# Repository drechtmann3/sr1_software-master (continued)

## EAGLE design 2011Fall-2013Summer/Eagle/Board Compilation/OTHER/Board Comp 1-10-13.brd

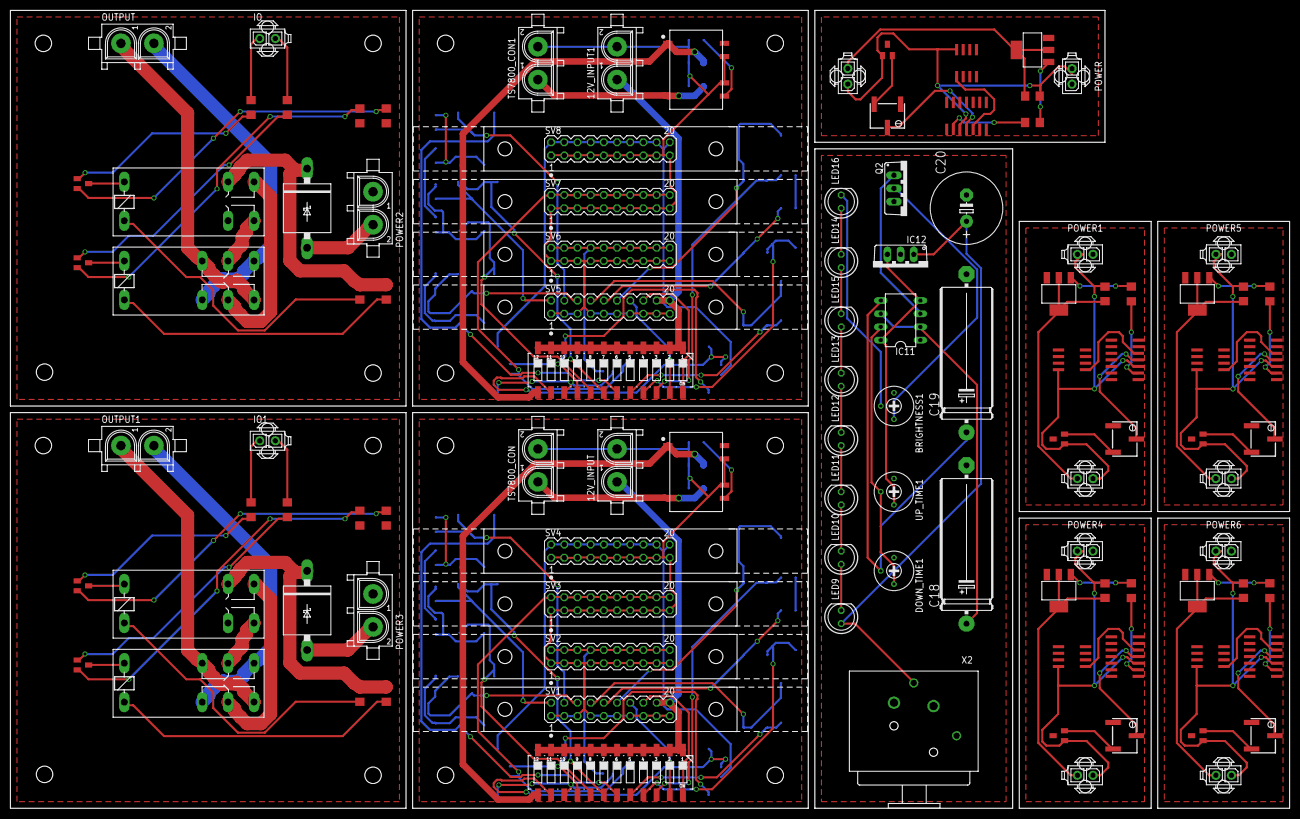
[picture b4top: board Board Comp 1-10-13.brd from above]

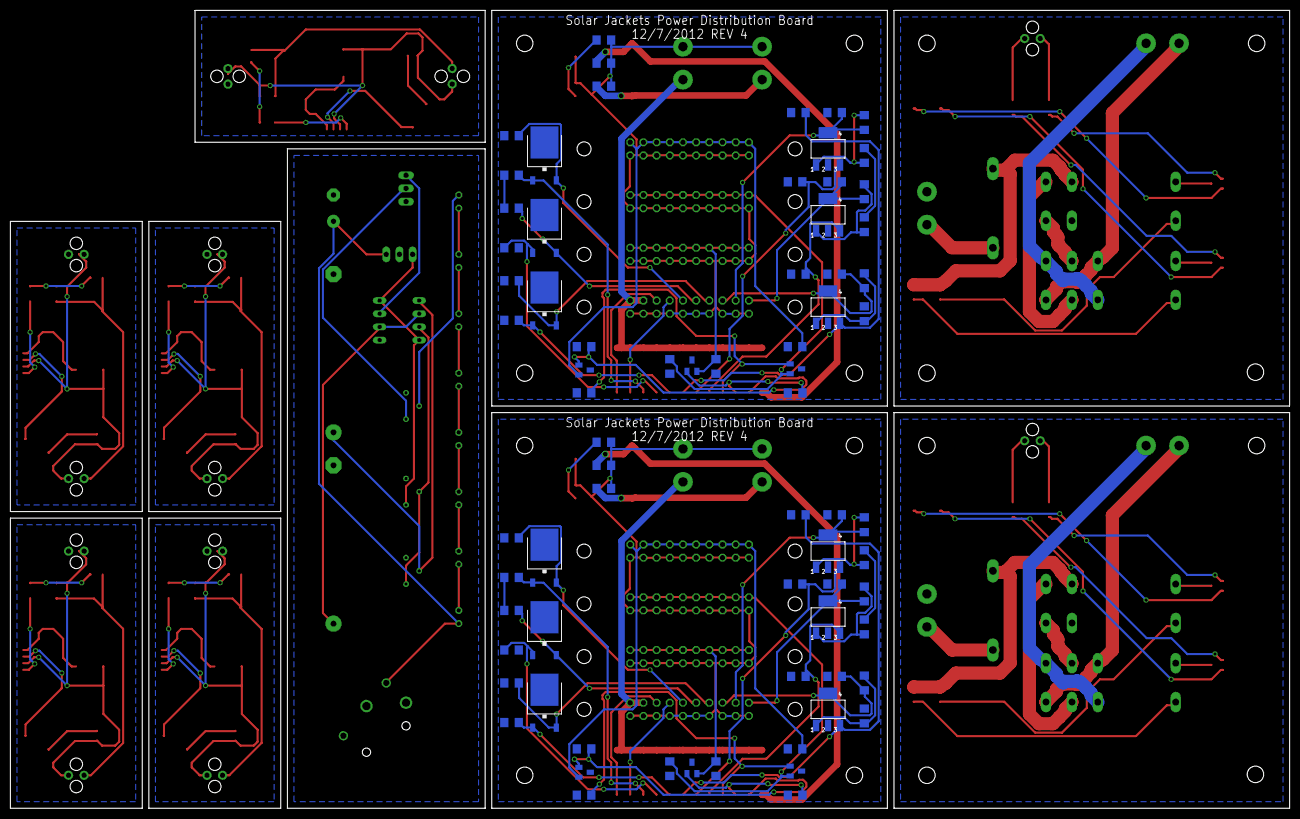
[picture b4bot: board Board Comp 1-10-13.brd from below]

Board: 2 copper layers, 246.4 x 153.7 mm, 179 parts (72 on the bottom side), 146 nets.

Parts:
3V1, 3V2, 3V3, 3V4, 3V5, 3V6: MAX6103; SOT23
12V_INPUT, 12V_INPUT1: 350759-4
317CAP1, 317CAP3, 317CAP4, 317CAP6, 317CAP9, 317CAP11: .33uF; C1206
317CAP2, 317CAP5, 317CAP7, 317CAP8, 317CAP10, 317CAP12, 6103CAP1, 6103CAP2, 6103CAP3, 6103CAP4, 6103CAP5, 6103CAP6, 6103CAP7, 6103CAP8, 6103CAP9, 6103CAP10, 6103CAP11, 6103CAP12: 1uF; C1206
BRIGHTNESS1: 10 k; RTRIM3339P
C1, C2, C15, C16, C21: 1 uF; C1206
C3, C4, C5, C6, C7, C8, C9, C10, C11, C12, C13, C14: 1uF; C1206
C18, C19: 1uF; E30-10
C20: 1000uF; E5-13
D1, D3: 6A4; P6T15
DOWN_TIME1: 10k; RTRIM3339P
IC1, IC2, IC9, IC10, IC13: LM339D; SO14
IC3, IC4, IC5, IC6, IC7, IC8: LM317; SOT223
IC11: ICM7555; DIL08
IC12: 7805TV; TO220V
IO, IO1: 794681-2
J1, J2, J3, J4, J5: 794681-2
K1, K3: G2R2
K2, K4: G2R2A
LED9, LED10, LED11, LED12, LED13, LED14, LED15, LED16: LED5MM
OUTPUT, OUTPUT1: 350428-1
POWER, POWER1, POWER4, POWER5, POWER6: 794681-2
POWER2, POWER3: 350428-1
PWR_1, PWR_2, PWR_3, PWR_4, PWR_5, PWR_6: 7805DT; TO252
Q2: IRF512; TO220BV
R1, R2, R27, R28, R29: 10k; RTRIMTS63Y
R3, R5, R7, R9, R11, R13: 220; R1206
R4, R6, R8, R10, R12, R14: 361; R1206
R15, R16, R17, R18, R21, R22, R23, R24: 1k; R1206
R19, R20, R25, R26: 0; R1206
S1, S2: 219-12; CTS-219-12
SV1, SV2, SV3, SV4, SV5, SV6, SV7, SV8: AMPLATCH-20; MA10-2
T1, T2, T3, T4: PMV56XN; SOT23
TS7800_CON, TS7800_CON1: 350759-4
U$1, U$5, U$11, U$15, U$19: 100; R1206
U$2, U$6, U$12, U$16, U$20: MAX6103; SOT23
U$3, U$7, U$13, U$17, U$21: NDT3055; SOT223
U$4, U$8, U$14, U$18, U$22: LM35; SO-08
U$9, U$10: V7805
UP_TIME1: 10k; RTRIM3339P
V7805_C1, V7805_C2, V7805_C3, V7805_C4, V7805_C5, V7805_C6: 1uF; C1206
X2: NC3FAH2

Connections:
3.3V1: 317CAP8.1, IC4.4, R7.1, SV1.6
3.3V1_EN: 317CAP3.1, IC4.3, S1.19
3.3V1_EN1: 317CAP1.1, IC3.3, S2.19
3.3V2: 317CAP10.1, IC5.4, R9.1, SV1.4
3.3V2_EN: 317CAP9.1, IC5.3, S1.18
3.3V2_EN1: 317CAP4.1, IC7.3, S2.18
3.3V3: 317CAP12.1, IC6.4, R11.1, SV1.2
3.3V3_EN: 317CAP11.1, IC6.3, S1.17
3.3V3_EN1: 317CAP6.1, IC8.3, S2.17
3.3V4: 317CAP7.1, IC8.4, R13.1, SV5.2
3.3V5: 317CAP2.1, IC3.4, R3.1, SV5.6
3.3V6: 317CAP5.1, IC7.4, R5.1, SV5.4
5V1: C4.1, PWR_1.2, SV1.12
5V1_EN: C3.1, PWR_1.1, S1.22
5V1_EN1: C9.1, PWR_4.1, S2.22
5V2: C6.1, PWR_2.2, SV1.10
5V2_EN: C5.1, PWR_2.1, S1.21
5V2_EN1: C11.1, PWR_5.1, S2.21
5V3: C7.1, PWR_3.2, SV1.8
5V3_EN: C8.1, PWR_3.1, S1.20
5V3_EN1: C14.1, PWR_6.1, S2.20
5V4: C13.1, PWR_6.2, SV5.8
5V5: C12.1, PWR_5.2, SV5.10
5V6: C10.1, PWR_4.2, SV5.12
5V7: IC11.4, IC11.8, IC12.3, UP_TIME1.3
12V: C1.1, IC1.3, J2.1, POWER.2, U$2.1, U$4.8
12V1: C2.1, IC2.3, J1.1, POWER1.2, U$6.1, U$8.8
12V1_EN: S1.24, SV1.16
12V1_EN1: S2.24, SV5.16
12V2: 12V_INPUT.1, S1.1, S1.2, S1.3, S1.4, S1.5, S1.6, S1.7, S1.8, S1.9, S1.10, S1.11, S1.12, SV1.18, SV1.20
12V2_EN: S1.23, SV1.14
12V2_EN1: S2.23, SV5.14
12V3: 12V_INPUT1.1, S2.1, S2.2, S2.3, S2.4, S2.5, S2.6, S2.7, S2.8, S2.9, S2.10, S2.11, S2.12, SV5.18, SV5.20
12V4: D3.C, K2.P1, R15.2, R16.2
12V5: D1.C, K4.P1, R21.2, R22.2
12V6: C21.1, IC13.3, J3.1, POWER4.2, U$12.1, U$14.8
12V7: C15.1, IC9.3, J4.1, POWER5.2, U$16.1, U$18.8
12V8: C16.1, IC10.3, J5.1, POWER6.2, U$20.1, U$22.8
12V_PRE: D3.A, POWER2.2
12V_PRE1: D1.A, POWER3.2
24V1: C20.+, IC12.1, LED9.A, X2.3
DIR: IO.2, R17.2
DIR1: IO1.2, R23.2
GND: IC1.12, POWER.1, R1.1, U$2.3, U$3.3, U$4.4
GND1: IC2.12, POWER1.1, R2.1, U$6.3, U$7.3, U$8.4
GND2: 3V3.3, 3V4.3, 3V5.3, 12V_INPUT.2, 317CAP3.2, 317CAP8.2, 317CAP9.2, 317CAP10.2, 317CAP11.2, 317CAP12.2, 6103CAP7.2, 6103CAP8.2, 6103CAP9.2, 6103CAP10.2, 6103CAP11.2, 6103CAP12.2, C3.2, C4.2, C5.2, C6.2, C7.2, C8.2, PWR_1.3, PWR_2.3, PWR_3.3, R8.2, R10.2, R12.2, SV1.1, SV1.3, SV1.5, SV1.7, SV1.9, SV1.11, SV1.13, SV1.15, SV1.17, SV1.19, SV2.1, SV2.3, SV2.5, SV2.7, SV2.9, SV2.11, SV2.13, SV2.15, SV2.17, SV2.19, SV3.1, SV3.3, SV3.5, SV3.7, SV3.9, SV3.11, SV3.13, SV3.15, SV3.17, SV3.19, SV4.1, SV4.3, SV4.5, SV4.7, SV4.9, SV4.11, SV4.13, SV4.15, SV4.17, SV4.19, TS7800_CON.2, U$9.7, U$9.9, V7805_C4.2, V7805_C5.2, V7805_C6.2
GND3: 3V1.3, 3V2.3, 3V6.3, 12V_INPUT1.2, 317CAP1.2, 317CAP2.2, 317CAP4.2, 317CAP5.2, 317CAP6.2, 317CAP7.2, 6103CAP1.2, 6103CAP2.2, 6103CAP3.2, 6103CAP4.2, 6103CAP5.2, 6103CAP6.2, C9.2, C10.2, C11.2, C12.2, C13.2, C14.2, PWR_4.3, PWR_5.3, PWR_6.3, R4.2, R6.2, R14.2, SV5.1, SV5.3, SV5.5, SV5.7, SV5.9, SV5.11, SV5.13, SV5.15, SV5.17, SV5.19, SV6.1, SV6.3, SV6.5, SV6.7, SV6.9, SV6.11, SV6.13, SV6.15, SV6.17, SV6.19, SV7.1, SV7.3, SV7.5, SV7.7, SV7.9, SV7.11, SV7.13, SV7.15, SV7.17, SV7.19, SV8.1, SV8.3, SV8.5, SV8.7, SV8.9, SV8.11, SV8.13, SV8.15, SV8.17, SV8.19, TS7800_CON1.2, U$10.7, U$10.9, V7805_C1.2, V7805_C2.2, V7805_C3.2
GND4: IC9.12, POWER5.1, R28.1, U$16.3, U$17.3, U$18.4
GND5: C18.-, C19.-, C20.-, IC11.1, IC12.2, Q2.S, X2.1
GND6: K2.P2, POWER2.1, R19.1, R20.1
GND7: K4.P2, POWER3.1, R25.1, R26.1
GND8: IC13.12, POWER4.1, R27.1, U$12.3, U$13.3, U$14.4
GND9: IC10.12, POWER6.1, R29.1, U$20.3, U$21.3, U$22.4
MOTOR+: K1.O2, K1.S1, OUTPUT.2
MOTOR+1: K3.O2, K3.S1, OUTPUT1.2
MOTOR-: K1.O1, K1.S2, OUTPUT.1
MOTOR-1: K3.O1, K3.S2, OUTPUT1.1
unnamed: IC1.2, U$1.1
unnamed: U$1.2, U$3.1
unnamed: IC1.4, R1.2
unnamed: R1.3, U$2.2
unnamed: C1.2, J2.2, U$3.2, U$3.4
unnamed: IC2.2, U$5.1
unnamed: IC2.4, R2.2
unnamed: IC1.5, U$4.1
unnamed: R2.3, U$6.2
unnamed: U$5.2, U$7.1
unnamed: C2.2, J1.2, U$7.2, U$7.4
unnamed: IC2.5, U$8.1
unnamed: IC4.1, R7.2, R8.1
unnamed: IC5.1, R9.2, R10.1
unnamed: IC6.1, R11.2, R12.1
unnamed: U$9.6, V7805_C4.1
unnamed: IC3.1, R3.2, R4.1
unnamed: IC7.1, R5.2, R6.1
unnamed: IC8.1, R13.2, R14.1
unnamed: U$10.6, V7805_C1.1
unnamed: IC9.2, U$15.1
unnamed: IC9.4, R28.2
unnamed: R28.3, U$16.2
unnamed: U$15.2, U$17.1
unnamed: C15.2, J4.2, U$17.2, U$17.4
unnamed: IC9.5, U$18.1
unnamed: IC10.2, U$19.1
unnamed: IC10.4, R29.2
unnamed: R29.3, U$20.2
unnamed: U$19.2, U$21.1
unnamed: C16.2, J5.2, U$21.2, U$21.4
unnamed: IC10.5, U$22.1
unnamed: C18.+, IC11.2, IC11.6
unnamed: C19.+, DOWN_TIME1.2, IC11.5
unnamed: DOWN_TIME1.3, IC11.7, UP_TIME1.2
unnamed: LED9.K, LED10.A
unnamed: LED10.K, LED11.A
unnamed: LED11.K, LED12.A
unnamed: LED12.K, LED13.A
unnamed: LED13.K, LED15.A
unnamed: LED14.A, LED15.K
unnamed: LED14.K, LED16.A
unnamed: BRIGHTNESS1.2, LED16.K
unnamed: BRIGHTNESS1.3, Q2.D
unnamed: IC11.3, Q2.G
unnamed: K1.P2, K2.S1
unnamed: K1.P1, K2.S2
unnamed: K1.1, R15.1
unnamed: K2.1, R16.1
unnamed: K1.2, T1.3
unnamed: K2.2, T2.3
unnamed: R18.1, T2.1
unnamed: R17.1, T1.1
unnamed: R19.2, T1.2
unnamed: R20.2, T2.2
unnamed: K3.P2, K4.S1
unnamed: K3.P1, K4.S2
unnamed: K3.1, R21.1
unnamed: K4.1, R22.1
unnamed: K3.2, T3.3
unnamed: K4.2, T4.3
unnamed: R24.1, T4.1
unnamed: R23.1, T3.1
unnamed: R25.2, T3.2
unnamed: R26.2, T4.2
unnamed: IC13.2, U$11.1
unnamed: IC13.4, R27.2
unnamed: R27.3, U$12.2
unnamed: U$11.2, U$13.1
unnamed: C21.2, J3.2, U$13.2, U$13.4
unnamed: IC13.5, U$14.1
ON: IO.1, R18.2
ON1: IO1.1, R24.2
TS7800_+: TS7800_CON.1, U$9.5, V7805_C6.1
TS7800_+1: TS7800_CON1.1, U$10.5, V7805_C3.1
TS7800_EN: S1.13, U$9.1, V7805_C5.1
TS7800_EN1: S2.13, U$10.1, V7805_C2.1
VREF1: 3V3.2, 6103CAP8.1, SV3.2, SV3.4, SV3.6, SV3.8, SV3.10, SV3.12, SV3.14, SV3.16, SV3.18, SV3.20
VREF1_EN: 3V3.1, 6103CAP7.1, S1.16
VREF1_EN1: 3V1.1, 6103CAP1.1, S2.16
VREF2: 3V4.2, 6103CAP10.1, SV2.2, SV2.4, SV2.6, SV2.8, SV2.10, SV2.12, SV2.14, SV2.16, SV2.18, SV2.20
VREF2_EN: 3V4.1, 6103CAP9.1, S1.15
VREF2_EN1: 3V2.1, 6103CAP3.1, S2.15
VREF3: 3V5.2, 6103CAP12.1, SV4.2, SV4.4, SV4.6, SV4.8, SV4.10, SV4.12, SV4.14, SV4.16, SV4.18, SV4.20
VREF3_EN: 3V5.1, 6103CAP11.1, S1.14
VREF3_EN1: 3V6.1, 6103CAP5.1, S2.14
VREF4: 3V1.2, 6103CAP2.1, SV7.2, SV7.4, SV7.6, SV7.8, SV7.10, SV7.12, SV7.14, SV7.16, SV7.18, SV7.20
VREF5: 3V2.2, 6103CAP4.1, SV6.2, SV6.4, SV6.6, SV6.8, SV6.10, SV6.12, SV6.14, SV6.16, SV6.18, SV6.20
VREF6: 3V6.2, 6103CAP6.1, SV8.2, SV8.4, SV8.6, SV8.8, SV8.10, SV8.12, SV8.14, SV8.16, SV8.18, SV8.20

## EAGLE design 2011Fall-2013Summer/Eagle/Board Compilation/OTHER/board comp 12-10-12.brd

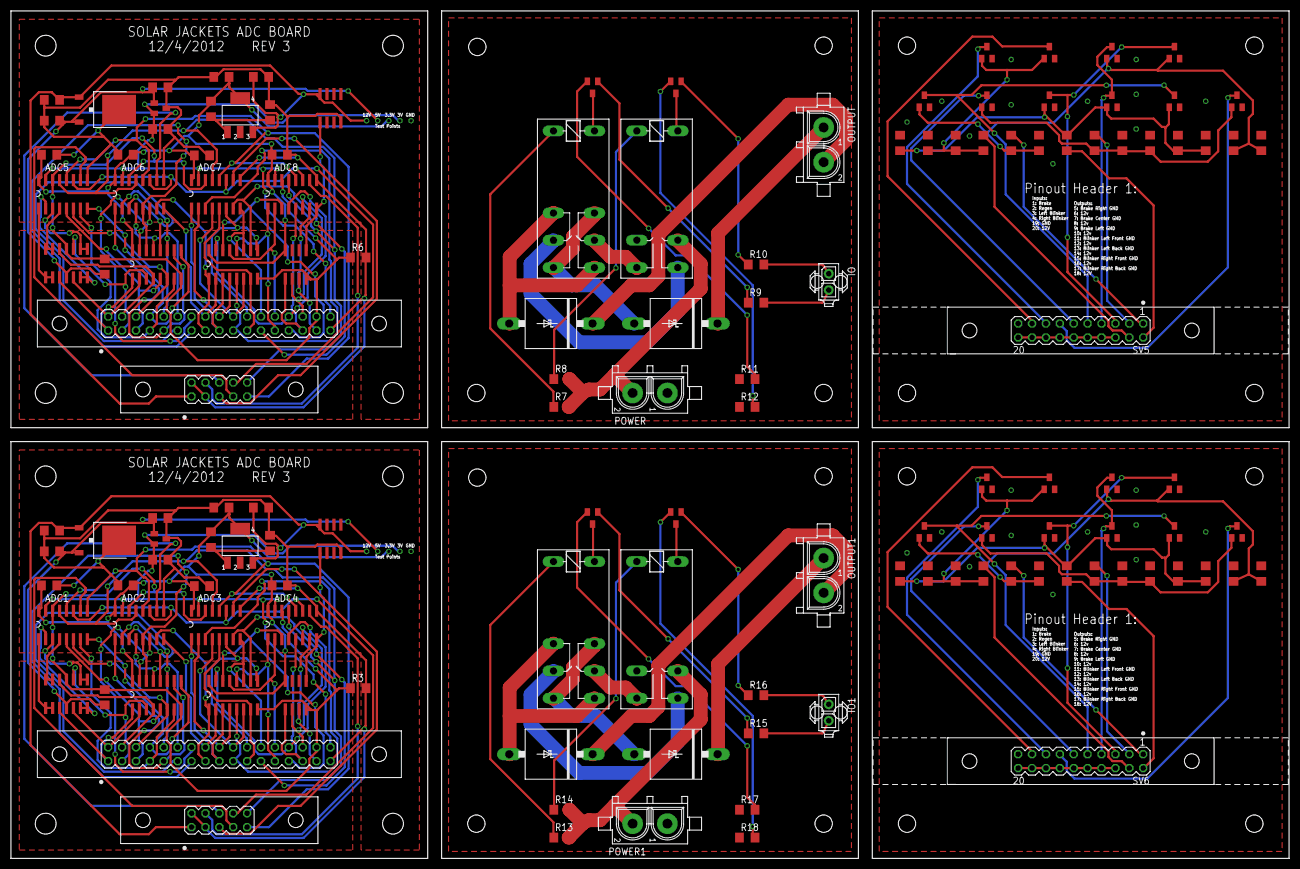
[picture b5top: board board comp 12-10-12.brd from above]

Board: 2 copper layers, 233.7 x 154.9 mm, 136 parts (0 on the bottom side), 170 nets.

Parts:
3V, 3V1: MAX6103; SOT23
5V, 5V1: LM7805TV; TO252
317CAP1, 317CAP3, 7805CAP1, 7805CAP4: .33uF; C1206
317CAP2, 317CAP4, 6103CAP1, 6103CAP2, 6103CAP3, 6103CAP4, 7805CAP2, 7805CAP3: 1uF; C1206
6484CAP1, 6484CAP2: .1uF; C1206
ADC1, ADC2, ADC3, ADC4, ADC5, ADC6, ADC7, ADC8: MCP-3008; SO16
ADC_CAP1, ADC_CAP2, ADC_CAP3, ADC_CAP4, ADC_CAP5, ADC_CAP6, ADC_CAP7, ADC_CAP8: .1uF; C1206
BLINKER-L1, BLINKER-L2, BLINKER-L3, BLINKER-L4: PMV56XN215; SOT23
BLINKER-R1, BLINKER-R2, BLINKER-R3, BLINKER-R4: PMV56XN215; SOT23
BRAKE-C1, BRAKE-C2, BRAKE-C3, BRAKE-C4: PMV56XN215; SOT23
BRAKE-L1, BRAKE-L2, BRAKE-L3, BRAKE-L4: PMV56XN215; SOT23
BRAKE-R1, BRAKE-R2, BRAKE-R3, BRAKE-R4: PMV56XN215; SOT23
D1, D2, D3, D4: 6A4; P6T15
IC1, IC2: LM317; SOT223
IO, IO1: 794681-2
K1, K3: G2R2
K2, K4: G2R2A
LMC6484_1, LMC6484_2: LMC6484; SO14
OUTPUT, OUTPUT1: 350428-1
POWER, POWER1: 350428-1
R1, R4: 220; R1206
R2, R5: 361; R1206
R3, R6, R11, R12, R17, R18: 0; R1206
R7, R8, R9, R10, R13, R14, R15, R16, R19, R20, R21, R22, R23, R24, R25, R26, R27, R28, R29, R30, R31, R32, R33, R34, R35, R36, R37, R38, R39, R40, R41, R42, R43, R44, R45, R46: 1k; R1206
SV1, SV3: MA17-2
SV2, SV4: MA05-2
SV5, SV6: AMPLATCH-20; MA10-2
T1, T2, T3, T4: PMV56XN; SOT23
U$1, U$3, U$6, U$7: SP720APP; SO16
U$2, U$5: LM35; SO-08
U$4, U$8: SP721APP; SO-08

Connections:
3.3V: 317CAP2.1, ADC1.16, ADC2.16, ADC3.16, ADC4.16, ADC_CAP1.1, ADC_CAP2.1, ADC_CAP3.1, ADC_CAP4.1, IC2.4, R1.1, U$6.16, U$7.16, U$8.8
3.3V1: 317CAP4.1, ADC5.16, ADC6.16, ADC7.16, ADC8.16, ADC_CAP5.1, ADC_CAP6.1, ADC_CAP7.1, ADC_CAP8.1, IC1.4, R4.1, U$1.16, U$3.16, U$4.8
5V: 3V.1, 5V.2, 6103CAP1.1, 6484CAP1.1, 7805CAP2.1, LMC6484_1.4
5V1: 3V1.1, 5V1.2, 6103CAP3.1, 6484CAP2.1, 7805CAP3.1, LMC6484_2.4
12V: 5V.1, 317CAP1.1, 7805CAP1.1, IC2.3, SV2.1, U$2.8
12V1: 5V1.1, 317CAP3.1, 7805CAP4.1, IC1.3, SV4.1, U$5.8
12V2: K2.P1, POWER.2, R7.2, R8.2
12V3: K4.P1, POWER1.2, R13.2, R14.2
12V4: SV5.6, SV5.8, SV5.10, SV5.12, SV5.14, SV5.16, SV5.18, SV5.20
12V5: SV6.6, SV6.8, SV6.10, SV6.12, SV6.14, SV6.16, SV6.18, SV6.20
A1: ADC1.1, LMC6484_1.1, LMC6484_1.2
A2: ADC1.2, LMC6484_1.6, LMC6484_1.7
A3: ADC1.3, LMC6484_1.8, LMC6484_1.9
A4: ADC1.4, LMC6484_1.13, LMC6484_1.14
A5: ADC5.1, LMC6484_2.1, LMC6484_2.2
A6: ADC5.2, LMC6484_2.6, LMC6484_2.7
A7: ADC5.3, LMC6484_2.8, LMC6484_2.9
A8: ADC5.4, LMC6484_2.13, LMC6484_2.14
AGND: 6484CAP1.2, ADC1.14, ADC2.14, ADC3.14, ADC4.14, LMC6484_1.11, R3.1, SV1.32, U$6.8, U$7.8, U$8.4
AGND1: 6484CAP2.2, ADC5.14, ADC6.14, ADC7.14, ADC8.14, LMC6484_2.11, R6.1, SV3.32, U$1.8, U$3.8, U$4.4
BLINKER_L: BLINKER-L1.1, BLINKER-L2.1, R23.2, R24.2, R32.2
BLINKER_L1: BLINKER-L3.1, BLINKER-L4.1, R37.2, R38.2, R46.2
BLINKER_L_BACK_-: BLINKER-L2.3, SV5.13
BLINKER_L_BACK_-1: BLINKER-L4.3, SV6.13
BLINKER_L_FRONT_-: BLINKER-L1.3, SV5.11
BLINKER_L_FRONT_-1: BLINKER-L3.3, SV6.11
BLINKER_R: BLINKER-R1.1, BLINKER-R2.1, R25.2, R26.2, R29.1
BLINKER_R1: BLINKER-R3.1, BLINKER-R4.1, R39.2, R40.2, R43.1
BLINKER_R_BACK_-: BLINKER-R2.3, SV5.17
BLINKER_R_BACK_-1: BLINKER-R4.3, SV6.17
BLINKER_R_FRONT_-: BLINKER-R1.3, SV5.15
BLINKER_R_FRONT_-1: BLINKER-R3.3, SV6.15
BRAKE: BRAKE-C1.1, BRAKE-L1.1, BRAKE-R1.1, R19.2, R21.2, R27.2, R31.2
BRAKE1: BRAKE-C4.1, BRAKE-L4.1, BRAKE-R3.1, R33.2, R35.2, R41.2, R45.2
BRAKE_C_-: BRAKE-C1.3, BRAKE-C2.3, SV5.7
BRAKE_C_-1: BRAKE-C3.3, BRAKE-C4.3, SV6.7
BRAKE_L_-: BRAKE-L1.3, BRAKE-L2.3, SV5.9
BRAKE_L_-1: BRAKE-L3.3, BRAKE-L4.3, SV6.9
BRAKE_REGEN: BRAKE-C2.1, BRAKE-L2.1, BRAKE-R2.1, R20.2, R22.2, R28.2, R30.1
BRAKE_REGEN1: BRAKE-C3.1, BRAKE-L3.1, BRAKE-R4.1, R34.2, R36.2, R42.2, R44.1
BRAKE_R_-: BRAKE-R1.3, BRAKE-R2.3, SV5.5
BRAKE_R_-1: BRAKE-R3.3, BRAKE-R4.3, SV6.5
DIR: IO.2, R9.2
DIR1: IO1.2, R15.2
GND: 3V.3, 5V.3, 317CAP1.2, 317CAP2.2, 6103CAP1.2, 6103CAP2.2, 7805CAP1.2, 7805CAP2.2, ADC1.9, ADC2.9, ADC3.9, ADC4.9, ADC_CAP1.2, ADC_CAP2.2, ADC_CAP3.2, ADC_CAP4.2, R2.2, R3.2, SV1.33, SV2.2, SV2.3, U$2.4
GND1: 3V1.3, 5V1.3, 317CAP3.2, 317CAP4.2, 6103CAP3.2, 6103CAP4.2, 7805CAP3.2, 7805CAP4.2, ADC5.9, ADC6.9, ADC7.9, ADC8.9, ADC_CAP5.2, ADC_CAP6.2, ADC_CAP7.2, ADC_CAP8.2, R5.2, R6.2, SV3.33, SV4.2, SV4.3, U$5.4
GND2: K2.P2, POWER.1, R11.1, R12.1
GND3: K4.P2, POWER1.1, R17.1, R18.1
GND4: BLINKER-L1.2, BLINKER-L2.2, BLINKER-R1.2, BLINKER-R2.2, BRAKE-C1.2, BRAKE-C2.2, BRAKE-L1.2, BRAKE-L2.2, BRAKE-R1.2, BRAKE-R2.2, R19.1, R20.1, R21.1, R22.1, R23.1, R24.1, R25.1, R26.1, R27.1, R28.1, SV5.19
GND5: BLINKER-L3.2, BLINKER-L4.2, BLINKER-R3.2, BLINKER-R4.2, BRAKE-C3.2, BRAKE-C4.2, BRAKE-L3.2, BRAKE-L4.2, BRAKE-R3.2, BRAKE-R4.2, R33.1, R34.1, R35.1, R36.1, R37.1, R38.1, R39.1, R40.1, R41.1, R42.1, SV6.19
IN1: LMC6484_1.3, SV1.1, U$6.1
IN2: LMC6484_1.5, SV1.2, U$6.2
IN3: LMC6484_1.10, SV1.3, U$6.3
IN4: LMC6484_1.12, SV1.4, U$6.4
IN5: ADC1.5, SV1.5, U$6.5
IN6: ADC1.6, SV1.6, U$6.6
IN7: ADC1.7, SV1.7, U$6.7
IN8: ADC1.8, SV1.8, U$6.9
IN9: ADC2.1, SV1.9, U$6.10
IN10: ADC2.2, SV1.10, U$6.11
IN11: ADC2.3, SV1.11, U$6.12
IN12: ADC2.4, SV1.12, U$6.13
IN13: ADC2.5, SV1.13, U$6.14
IN14: ADC2.6, SV1.14, U$6.15
IN15: ADC2.7, SV1.15, U$7.1
IN16: ADC2.8, SV1.16, U$7.2
IN17: ADC3.1, SV1.17, U$7.3
IN18: ADC3.2, SV1.18, U$7.4
IN19: ADC3.3, SV1.19, U$7.5
IN20: ADC3.4, SV1.20, U$7.6
IN21: ADC3.5, SV1.21, U$7.7
IN22: ADC3.6, SV1.22, U$7.9
IN23: ADC3.7, SV1.23, U$7.10
IN24: ADC3.8, SV1.24, U$7.11
IN25: ADC4.1, SV1.25, U$7.12
IN26: ADC4.2, SV1.26, U$7.13
IN27: ADC4.3, SV1.27, U$7.14
IN28: ADC4.4, SV1.28, U$7.15
IN29: ADC4.5, SV1.29, U$8.1
IN30: ADC4.6, SV1.30, U$8.2
IN31: ADC4.7, SV1.31, U$8.3
IN32: ADC4.8, U$2.1, U$8.5
IN33: LMC6484_2.3, SV3.1, U$1.1
IN34: LMC6484_2.5, SV3.2, U$1.2
IN35: LMC6484_2.10, SV3.3, U$1.3
IN36: LMC6484_2.12, SV3.4, U$1.4
IN37: ADC5.8, SV3.8, U$1.9
IN38: ADC5.7, SV3.7, U$1.7
IN39: ADC5.6, SV3.6, U$1.6
IN40: ADC5.5, SV3.5, U$1.5
IN41: ADC6.2, SV3.10, U$1.11
IN42: ADC6.1, SV3.9, U$1.10
IN43: ADC6.5, SV3.13, U$1.14
IN44: ADC6.6, SV3.14, U$1.15
IN45: ADC7.8, SV3.24, U$3.11
IN46: ADC7.7, SV3.23, U$3.10
IN47: ADC7.5, SV3.21, U$3.7
IN48: ADC7.6, SV3.22, U$3.9
IN49: ADC7.4, SV3.20, U$3.6
IN50: ADC7.3, SV3.19, U$3.5
IN51: ADC7.1, SV3.17, U$3.3
IN52: ADC7.2, SV3.18, U$3.4
IN53: ADC8.1, SV3.25, U$3.12
IN54: ADC8.2, SV3.26, U$3.13
IN55: ADC8.4, SV3.28, U$3.15
IN56: ADC8.3, SV3.27, U$3.14
IN57: ADC8.8, U$4.5, U$5.1
IN58: ADC8.7, SV3.31, U$4.3
IN59: ADC8.5, SV3.29, U$4.1
IN60: ADC8.6, SV3.30, U$4.2
IN61: ADC6.8, SV3.16, U$3.2
IN62: ADC6.7, SV3.15, U$3.1
IN63: ADC6.3, SV3.11, U$1.12
IN64: ADC6.4, SV3.12, U$1.13
MOTOR+: D2.C, OUTPUT.2
MOTOR+1: D4.C, OUTPUT1.2
MOTOR+_PRE: D2.A, K1.O2, K1.S1
MOTOR+_PRE1: D4.A, K3.O2, K3.S1
MOTOR-: D1.C, OUTPUT.1
MOTOR-1: D3.C, OUTPUT1.1
MOTOR-_PRE: D1.A, K1.O1, K1.S2
MOTOR-_PRE1: D3.A, K3.O1, K3.S2
unnamed: IC2.1, R1.2, R2.1
unnamed: IC1.1, R4.2, R5.1
unnamed: K1.P2, K2.S1
unnamed: K1.P1, K2.S2
unnamed: K1.1, R7.1
unnamed: K2.1, R8.1
unnamed: K1.2, T1.3
unnamed: K2.2, T2.3
unnamed: R10.1, T2.1
unnamed: R9.1, T1.1
unnamed: R11.2, T1.2
unnamed: R12.2, T2.2
unnamed: K3.P2, K4.S1
unnamed: K3.P1, K4.S2
unnamed: K3.1, R13.1
unnamed: K4.1, R14.1
unnamed: K3.2, T3.3
unnamed: K4.2, T4.3
unnamed: R16.1, T4.1
unnamed: R15.1, T3.1
unnamed: R17.2, T3.2
unnamed: R18.2, T4.2
unnamed: R30.2, SV5.2
unnamed: R29.2, SV5.4
unnamed: R31.1, SV5.1
unnamed: R32.1, SV5.3
unnamed: R44.2, SV6.2
unnamed: R43.2, SV6.4
unnamed: R45.1, SV6.1
unnamed: R46.1, SV6.3
ON: IO.1, R10.2
ON1: IO1.1, R16.2
SPI_CLK: ADC1.13, ADC2.13, ADC3.13, ADC4.13, SV2.10
SPI_CLK1: ADC5.13, ADC6.13, ADC7.13, ADC8.13, SV4.10
SPI_CS1: ADC1.10, SV2.7
SPI_CS2: ADC2.10, SV2.6
SPI_CS3: ADC3.10, SV2.5
SPI_CS4: ADC4.10, SV2.4
SPI_CS5: ADC5.10, SV4.7
SPI_CS6: ADC6.10, SV4.6
SPI_CS7: ADC8.10, SV4.4
SPI_CS8: ADC7.10, SV4.5
SPI_DIN: ADC1.11, ADC2.11, ADC3.11, ADC4.11, SV2.8
SPI_DIN1: ADC5.11, ADC6.11, ADC7.11, ADC8.11, SV4.8
SPI_DOUT: ADC1.12, ADC2.12, ADC3.12, ADC4.12, SV2.9
SPI_DOUT1: ADC5.12, ADC6.12, ADC7.12, ADC8.12, SV4.9
VREF: 3V.2, 6103CAP2.1, ADC1.15, ADC2.15, ADC3.15, ADC4.15, SV1.34
VREF1: 3V1.2, 6103CAP4.1, ADC5.15, ADC6.15, ADC7.15, ADC8.15, SV3.34

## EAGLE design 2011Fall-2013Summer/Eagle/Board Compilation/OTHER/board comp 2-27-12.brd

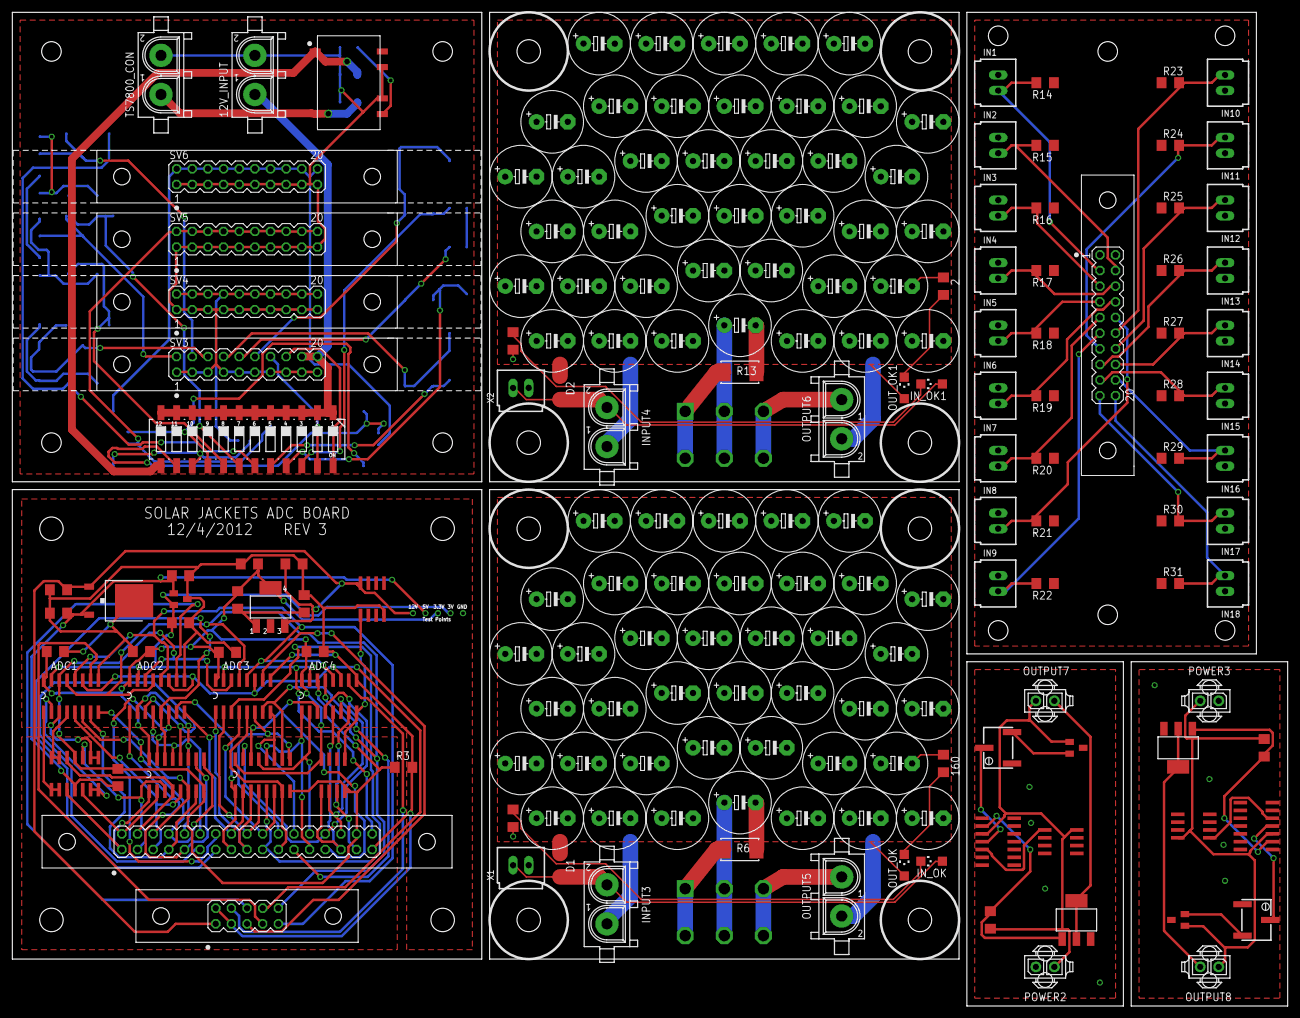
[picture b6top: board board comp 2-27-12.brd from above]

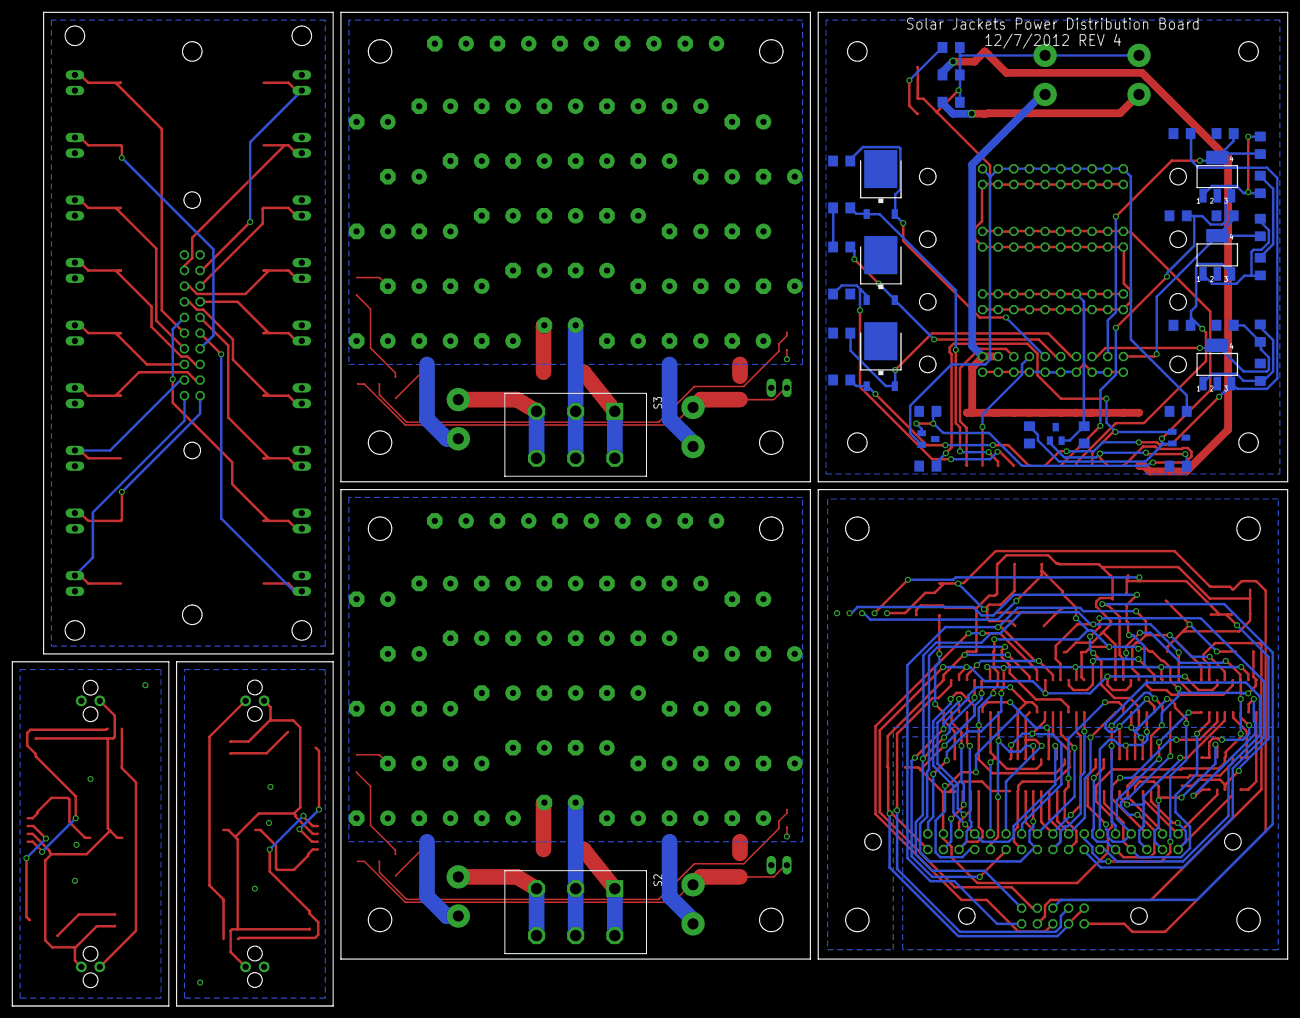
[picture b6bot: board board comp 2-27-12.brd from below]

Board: 2 copper layers, 207.0 x 161.3 mm, 225 parts (38 on the bottom side), 126 nets.

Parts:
1, 3: 160; R1206
2, 160: R1206
3V, 3V3, 3V4, 3V5: MAX6103; SOT23
5V: LM7805TV; TO252
12V_INPUT: 350759-4
317CAP1, 317CAP3, 317CAP9, 317CAP11, 7805CAP1: .33uF; C1206
317CAP2, 317CAP8, 317CAP10, 317CAP12, 6103CAP1, 6103CAP2, 6103CAP7, 6103CAP8, 6103CAP9, 6103CAP10, 6103CAP11, 6103CAP12, 7805CAP2: 1uF; C1206
6484CAP1: .1uF; C1206
ADC1, ADC2, ADC3, ADC4: MCP-3008; SO16
ADC_CAP1, ADC_CAP2, ADC_CAP3, ADC_CAP4: .1uF; C1206
C1, C2, C3, C4, C5, C6: 1uF; C1206
C34, C35, C36, C37, C38, C39, C40, C41, C42, C43, C44, C45, C46, C47, C48, C49, C50, C51, C52, C53, C54, C55, C56, C57, C58, C59, C60, C61, C62, C63, C64, C65, C66, C67, C68, C69, C70, C71, C72, C73, C74, C75, C76, C77, C78, C79, C80, C81, C82, C83, C84, C85, C86, C87, C88, C89, C90, C91, C92, C93, C94, C95, C96, C97, C98, C99, C100, C101, C102, C103, C104, C105, C106, C107, C108, C109, C110, C111, C112, C113: E5-10,5
D1, D2: SOD123
IC2, IC4, IC5, IC6: LM317; SOT223
IC10, IC11: LM339D; SO14
IN1, IN2, IN3, IN4, IN5, IN6, IN7, IN8, IN9, IN10, IN11, IN12, IN13, IN14, IN15, IN16, IN17, IN18: C-GRID-02-70543; 70543-02
INPUT3, INPUT4: 350428-1
IN_OK, IN_OK1: CHIPLED_1206
LMC6484_1: LMC6484; SO14
OUTPUT5, OUTPUT6: 350428-1
OUTPUT7, OUTPUT8: 794681-2
OUT_OK, OUT_OK1: CHIPLED_1206
POWER2, POWER3: 794681-2
PWR_1, PWR_2, PWR_3: 7805DT; TO252
R1, R7, R9, R11: 220; R1206
R2, R8, R10, R12: 361; R1206
R3: 0; R1206
R6, R13: WSC2515
R14, R15, R16, R17, R18, R19, R20, R21, R22, R23, R24, R25, R26, R27, R28, R29, R30, R31: 1K; R1206
R32, R33: 10k; RTRIMTS63Y
S1: 219-12; CTS-219-12
S2, S3: SLIDE_SWITCH
SV1: MA17-2
SV2: AMP_LATCH_10; MA05-2
SV3, SV4, SV5, SV6: AMPLATCH-20; MA10-2
TS7800_CON: 350759-4
U$1: V7805
U$2, U$18, U$22: LM35; SO-08
U$6, U$7: SP720APP; SO16
U$8: SP721APP; SO-08
U$14: AMP_LATCH-20; MA10-2
U$15, U$19: 100; R1206
U$16, U$20: MAX6103; SOT23
U$17, U$21: NDT3055; SOT223
V7805_C4, V7805_C5, V7805_C6: 1uF; C1206
X1, X2: C-GRID-02-70543; 70543-02

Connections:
3.3V: 317CAP2.1, ADC1.16, ADC2.16, ADC3.16, ADC4.16, ADC_CAP1.1, ADC_CAP2.1, ADC_CAP3.1, ADC_CAP4.1, IC2.4, R1.1, U$6.16, U$7.16, U$8.8
3.3V1: 317CAP8.1, IC4.4, R7.1, SV3.6
3.3V1_EN: 317CAP3.1, IC4.3, S1.19
3.3V2: 317CAP10.1, IC5.4, R9.1, SV3.4
3.3V2_EN: 317CAP9.1, IC5.3, S1.18
3.3V3: 317CAP12.1, IC6.4, R11.1, SV3.2
3.3V3_EN: 317CAP11.1, IC6.3, S1.17
3.3V7: IN1.1, IN2.1, IN3.1, IN4.1, IN5.1, IN6.1, IN7.1, IN8.1, IN9.1, IN10.1, IN11.1, IN12.1, IN13.1, IN14.1, IN15.1, IN16.1, IN17.1, IN18.1, U$14.1
5V: 3V.1, 5V.2, 6103CAP1.1, 6484CAP1.1, 7805CAP2.1, LMC6484_1.4
5V1: C2.1, PWR_1.2, SV3.12
5V1_EN: C1.1, PWR_1.1, S1.22
5V2: C4.1, PWR_2.2, SV3.10
5V2_EN: C3.1, PWR_2.1, S1.21
5V3: C6.1, PWR_3.2, SV3.8
5V3_EN: C5.1, PWR_3.1, S1.20
5V4: C34.+, C35.+, C36.+, C37.+, C38.+, C39.+, C40.+, C41.+, C42.+, C43.+, C44.+, C45.+, C46.+, C47.+, C48.+, C49.+, C50.+, C51.+, C52.+, C53.+, C54.+, C55.+, C56.+, C57.+, C58.+, C59.+, C60.+, C61.+, C62.+, C63.+, C64.+, C65.+, C66.+, C67.+, C68.+, C69.+, C70.+, C71.+, C72.+, C73.+, D1.C, OUT_OK.A, S2.2, S2.5
5V5: C74.+, C75.+, C76.+, C77.+, C78.+, C79.+, C80.+, C81.+, C82.+, C83.+, C84.+, C85.+, C86.+, C87.+, C88.+, C89.+, C90.+, C91.+, C92.+, C93.+, C94.+, C95.+, C96.+, C97.+, C98.+, C99.+, C100.+, C101.+, C102.+, C103.+, C104.+, C105.+, C106.+, C107.+, C108.+, C109.+, C110.+, C111.+, C112.+, C113.+, D2.C, OUT_OK1.A, S3.2, S3.5
12V: 5V.1, 317CAP1.1, 7805CAP1.1, IC2.3, SV2.1, U$2.8
12V1: 12V_INPUT.1, S1.1, S1.2, S1.3, S1.4, S1.5, S1.6, S1.7, S1.8, S1.9, S1.10, S1.11, S1.12, SV3.18, SV3.20
12V1_EN: S1.24, SV3.16
12V2_EN: S1.23, SV3.14
12V4: IC10.3, OUTPUT7.1, POWER2.2, U$15.2, U$16.1, U$18.8
12V5: IC11.3, OUTPUT8.1, POWER3.2, U$19.2, U$20.1, U$22.8
A1: ADC1.1, LMC6484_1.1, LMC6484_1.2
A2: ADC1.2, LMC6484_1.6, LMC6484_1.7
A3: ADC1.3, LMC6484_1.8, LMC6484_1.9
A4: ADC1.4, LMC6484_1.13, LMC6484_1.14
AGND: 6484CAP1.2, ADC1.14, ADC2.14, ADC3.14, ADC4.14, LMC6484_1.11, R3.1, SV1.32, U$6.8, U$7.8, U$8.4
GND: 3V.3, 5V.3, 317CAP1.2, 317CAP2.2, 6103CAP1.2, 6103CAP2.2, 7805CAP1.2, 7805CAP2.2, ADC1.9, ADC2.9, ADC3.9, ADC4.9, ADC_CAP1.2, ADC_CAP2.2, ADC_CAP3.2, ADC_CAP4.2, R2.2, R3.2, SV1.33, SV2.2, SV2.3, U$2.4
GND1: 3V3.3, 3V4.3, 3V5.3, 12V_INPUT.2, 317CAP3.2, 317CAP8.2, 317CAP9.2, 317CAP10.2, 317CAP11.2, 317CAP12.2, 6103CAP7.2, 6103CAP8.2, 6103CAP9.2, 6103CAP10.2, 6103CAP11.2, 6103CAP12.2, C1.2, C2.2, C3.2, C4.2, C5.2, C6.2, PWR_1.3, PWR_2.3, PWR_3.3, R8.2, R10.2, R12.2, SV3.1, SV3.3, SV3.5, SV3.7, SV3.9, SV3.11, SV3.13, SV3.15, SV3.17, SV3.19, SV4.1, SV4.3, SV4.5, SV4.7, SV4.9, SV4.11, SV4.13, SV4.15, SV4.17, SV4.19, SV5.1, SV5.3, SV5.5, SV5.7, SV5.9, SV5.11, SV5.13, SV5.15, SV5.17, SV5.19, SV6.1, SV6.3, SV6.5, SV6.7, SV6.9, SV6.11, SV6.13, SV6.15, SV6.17, SV6.19, TS7800_CON.2, U$1.7, U$1.9, V7805_C4.2, V7805_C5.2, V7805_C6.2
GND7: 1.1, 160.1, C34.-, C35.-, C36.-, C37.-, C38.-, C39.-, C40.-, C41.-, C42.-, C43.-, C44.-, C45.-, C46.-, C47.-, C48.-, C49.-, C50.-, C51.-, C52.-, C53.-, C54.-, C55.-, C56.-, C57.-, C58.-, C59.-, C60.-, C61.-, C62.-, C63.-, C64.-, C65.-, C66.-, C67.-, C68.-, C69.-, C70.-, C71.-, C72.-, C73.-, INPUT3.1, OUTPUT5.2, R6.2
GND8: 2.1, 3.1, C74.-, C75.-, C76.-, C77.-, C78.-, C79.-, C80.-, C81.-, C82.-, C83.-, C84.-, C85.-, C86.-, C87.-, C88.-, C89.-, C90.-, C91.-, C92.-, C93.-, C94.-, C95.-, C96.-, C97.-, C98.-, C99.-, C100.-, C101.-, C102.-, C103.-, C104.-, C105.-, C106.-, C107.-, C108.-, C109.-, C110.-, C111.-, C112.-, C113.-, INPUT4.1, OUTPUT6.2, R13.2
GND9: R14.1, R15.1, R16.1, R17.1, R18.1, R19.1, R20.1, R21.1, R22.1, R23.1, R24.1, R25.1, R26.1, R27.1, R28.1, R29.1, R30.1, R31.1, U$14.2
GND10: IC10.12, POWER2.1, R32.1, U$16.3, U$17.3, U$18.4
GND11: IC11.12, POWER3.1, R33.1, U$20.3, U$21.3, U$22.4
IN1: LMC6484_1.3, SV1.1, U$6.1
IN2: LMC6484_1.5, SV1.2, U$6.2
IN3: LMC6484_1.10, SV1.3, U$6.3
IN4: LMC6484_1.12, SV1.4, U$6.4
IN5: ADC1.5, SV1.5, U$6.5
IN6: ADC1.6, SV1.6, U$6.6
IN7: ADC1.7, SV1.7, U$6.7
IN8: ADC1.8, SV1.8, U$6.9
IN9: ADC2.1, SV1.9, U$6.10
IN10: ADC2.2, SV1.10, U$6.11
IN11: ADC2.3, SV1.11, U$6.12
IN12: ADC2.4, SV1.12, U$6.13
IN13: ADC2.5, SV1.13, U$6.14
IN14: ADC2.6, SV1.14, U$6.15
IN15: ADC2.7, SV1.15, U$7.1
IN16: ADC2.8, SV1.16, U$7.2
IN17: ADC3.1, SV1.17, U$7.3
IN18: ADC3.2, SV1.18, U$7.4
IN19: ADC3.3, SV1.19, U$7.5
IN20: ADC3.4, SV1.20, U$7.6
IN21: ADC3.5, SV1.21, U$7.7
IN22: ADC3.6, SV1.22, U$7.9
IN23: ADC3.7, SV1.23, U$7.10
IN24: ADC3.8, SV1.24, U$7.11
IN25: ADC4.1, SV1.25, U$7.12
IN26: ADC4.2, SV1.26, U$7.13
IN27: ADC4.3, SV1.27, U$7.14
IN28: ADC4.4, SV1.28, U$7.15
IN29: ADC4.5, SV1.29, U$8.1
IN30: ADC4.6, SV1.30, U$8.2
IN31: ADC4.7, SV1.31, U$8.3
IN32: ADC4.8, U$2.1, U$8.5
IN33: IN1.2, R14.2, U$14.3
IN34: IN14.2, R27.2, U$14.16
IN35: IN15.2, R28.2, U$14.17
IN36: IN7.2, R20.2, U$14.9
IN37: IN11.2, R24.2, U$14.13
IN38: IN18.2, R31.2, U$14.20
IN39: IN16.2, R29.2, U$14.18
IN40: IN6.2, R19.2, U$14.8
IN41: IN5.2, R18.2, U$14.7
IN42: IN12.2, R25.2, U$14.14
IN43: IN13.2, R26.2, U$14.15
IN44: IN2.2, R15.2, U$14.4
IN45: IN3.2, R16.2, U$14.5
IN46: IN17.2, R30.2, U$14.19
IN47: IN10.2, R23.2, U$14.12
IN48: IN9.2, R22.2, U$14.11
IN49: IN8.2, R21.2, U$14.10
IN50: IN4.2, R17.2, U$14.6
unnamed: IC2.1, R1.2, R2.1
unnamed: U$1.6, V7805_C4.1
unnamed: IC4.1, R7.2, R8.1
unnamed: IC5.1, R9.2, R10.1
unnamed: IC6.1, R11.2, R12.1
unnamed: 160.2, OUT_OK.C
unnamed: OUTPUT5.1, S2.3, S2.4
unnamed: D1.A, INPUT3.2, IN_OK.A, X1.1
unnamed: R6.1, S2.1, S2.6
unnamed: 1.2, IN_OK.C
unnamed: 2.2, OUT_OK1.C
unnamed: OUTPUT6.1, S3.3, S3.4
unnamed: D2.A, INPUT4.2, IN_OK1.A, X2.1
unnamed: R13.1, S3.1, S3.6
unnamed: 3.2, IN_OK1.C
unnamed: IC10.2, U$15.1, U$17.1
unnamed: IC10.4, R32.2
unnamed: R32.3, U$16.2
unnamed: OUTPUT7.2, U$17.2, U$17.4
unnamed: IC10.5, U$18.1
unnamed: IC11.2, U$19.1, U$21.1
unnamed: IC11.4, R33.2
unnamed: R33.3, U$20.2
unnamed: OUTPUT8.2, U$21.2, U$21.4
unnamed: IC11.5, U$22.1
SPI_CLK: ADC1.13, ADC2.13, ADC3.13, ADC4.13, SV2.10
SPI_CS1: ADC1.10, SV2.7
SPI_CS2: ADC2.10, SV2.6
SPI_CS3: ADC3.10, SV2.5
SPI_CS4: ADC4.10, SV2.4
SPI_DIN: ADC1.11, ADC2.11, ADC3.11, ADC4.11, SV2.8
SPI_DOUT: ADC1.12, ADC2.12, ADC3.12, ADC4.12, SV2.9
TS7800_+: TS7800_CON.1, U$1.5, V7805_C6.1
TS7800_EN: S1.13, U$1.1, V7805_C5.1
VREF: 3V.2, 6103CAP2.1, ADC1.15, ADC2.15, ADC3.15, ADC4.15, SV1.34
VREF1: 3V3.2, 6103CAP8.1, SV5.2, SV5.4, SV5.6, SV5.8, SV5.10, SV5.12, SV5.14, SV5.16, SV5.18, SV5.20
VREF1_EN: 3V3.1, 6103CAP7.1, S1.16
VREF2: 3V4.2, 6103CAP10.1, SV4.2, SV4.4, SV4.6, SV4.8, SV4.10, SV4.12, SV4.14, SV4.16, SV4.18, SV4.20
VREF2_EN: 3V4.1, 6103CAP9.1, S1.15
VREF3: 3V5.2, 6103CAP12.1, SV6.2, SV6.4, SV6.6, SV6.8, SV6.10, SV6.12, SV6.14, SV6.16, SV6.18, SV6.20
VREF3_EN: 3V5.1, 6103CAP11.1, S1.14
